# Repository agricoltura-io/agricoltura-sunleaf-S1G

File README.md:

# agricoltura-sunleaf-S1G
A new generation of the SunLeaf platform based on STM32 S1G radio module

Quick Specs:
- ST Microelectronics SPSGRF-915 STM32 ARM Cortex M0 915MHZ RF Module
- BQ240210 Lithium Ion Solar/USB charge controller and battery management 
- 500mA Lithium Polymer battery with thermistor 
- I2C ports
- UART ports
- Analog ports

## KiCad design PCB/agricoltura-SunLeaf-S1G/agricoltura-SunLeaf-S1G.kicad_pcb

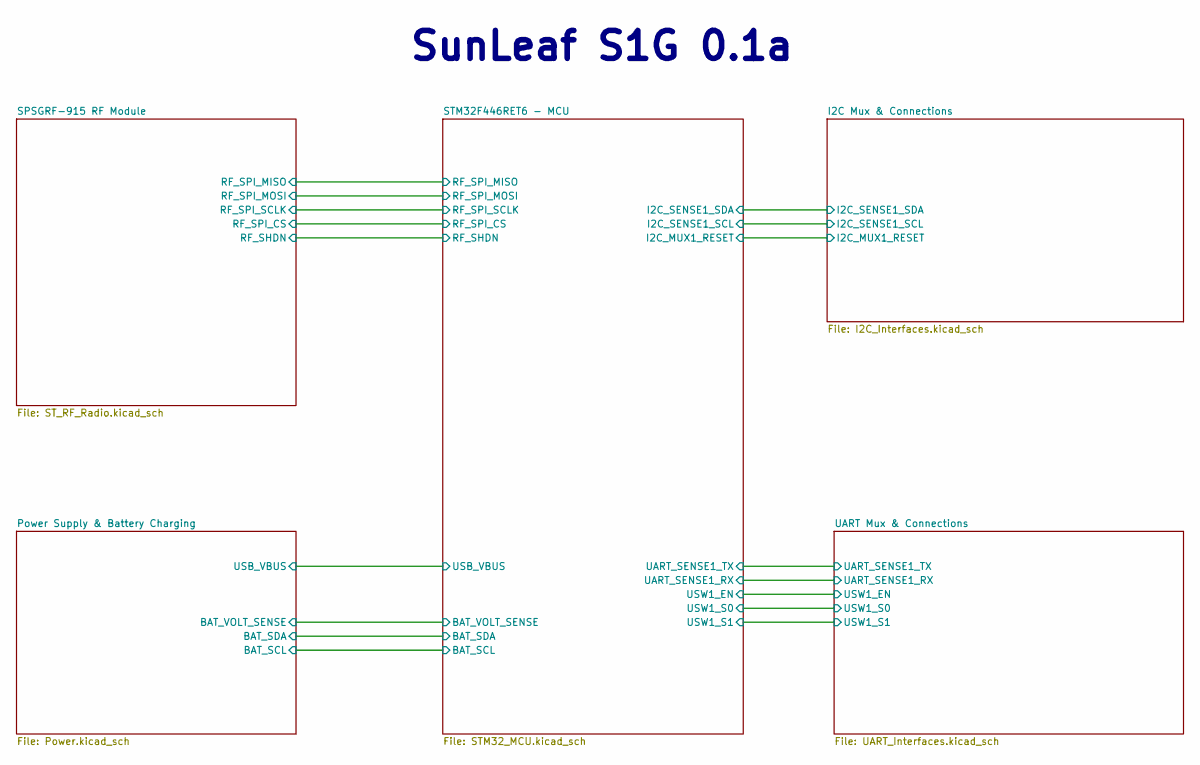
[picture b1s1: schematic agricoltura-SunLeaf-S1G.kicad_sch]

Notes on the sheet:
SunLeaf S1G 0.1a

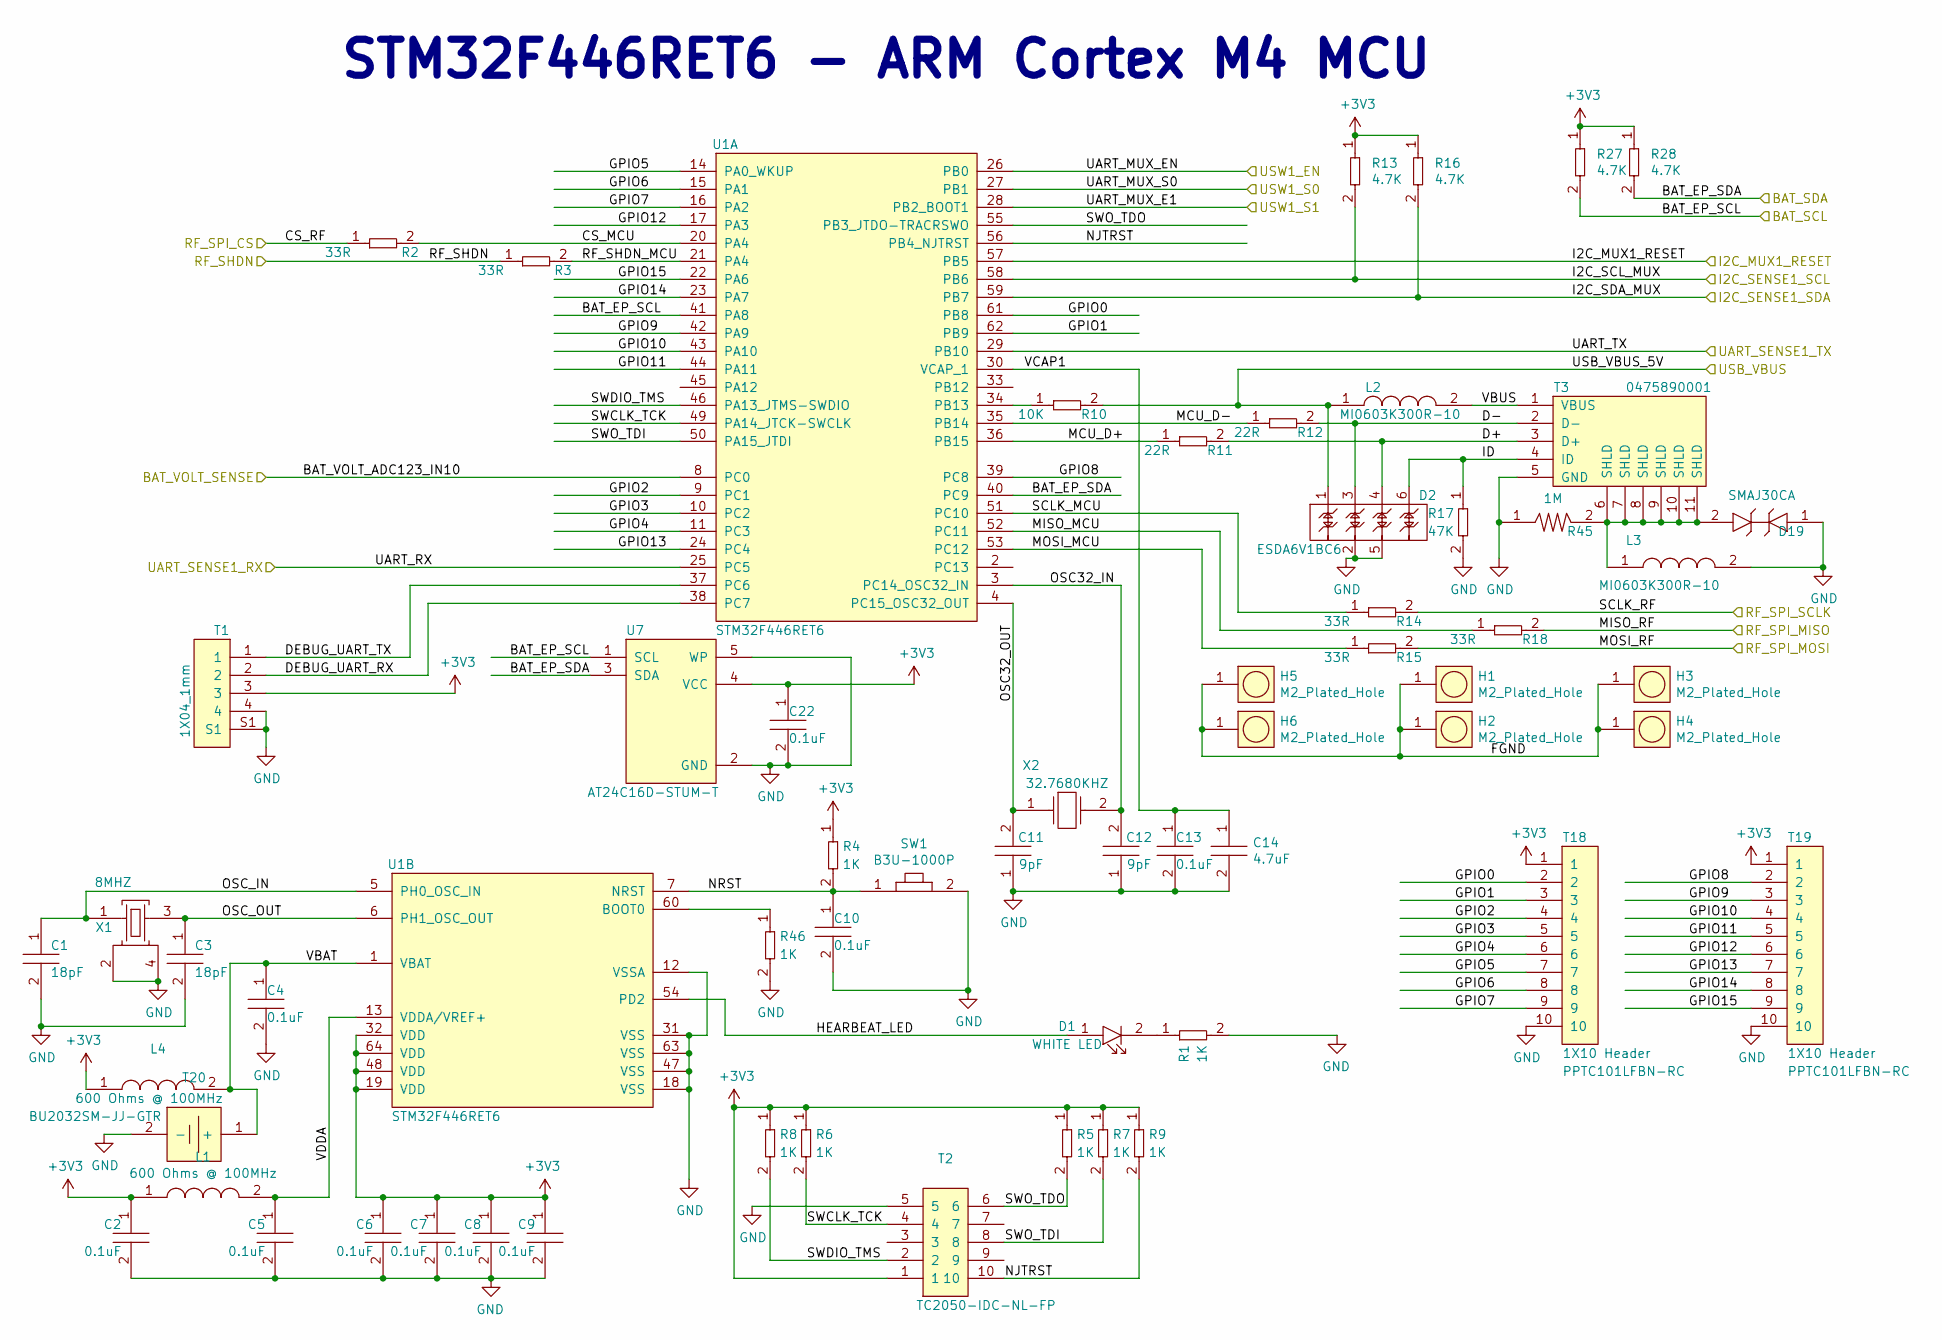
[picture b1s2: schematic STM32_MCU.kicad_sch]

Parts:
C1, C3: GCM1555C1H180GA16D; C0402; Tolerance 2%; Voltage 50V; MFR# GCM1555C1H180GA16D
C2, C4, C5, C6, C7, C8, C9, C10, C13, C22: C0402C104K9PACTU; R0402; Tolerance 10%; Voltage 6.3V; MFR# C0402C104K9PACTU
C11, C12: CL05C090CB5NNNC; C0402; Tolerance ±0.25pF; Voltage 50V; MFR# CL05C090CB5NNNC
C14: GRM155R60J475ME47D; C0402; Tolerance 20%; Voltage 6.3V; MFR# GRM155R60J475ME47D
D1: LW_Q38G_Q1OO_3K6L_1; LED0603; Tolerance *; Voltage 2.85V; MFR# LW Q38G-Q1OO-3K6L-1
D2: ESDA6V1BC6; SOT-23-6_Handsoldering; Tolerance *; Voltage 5V/6.1VBreakdown; MFR# ESDA6V1BC6
D19: SMAJ30CA; Tolerance *; Voltage 30V Clamp; MFR# SMAJ30CA
H1, H2, H3, H4, H5, H6: M2_Plated_Hole; M2_HOLE; Tolerance *; Voltage *; MFR# *
L1, L4: BLM15HG601SN1D; Tolerance *; Voltage *; MFR# BLM15HG601SN1D
L2, L3: MI0603K300R-10; Tolerance *; Voltage *; MFR# MI0603K300R-10
R1, R4, R5, R6, R7, R8, R9, R46: RC0402FR-071KL; R0402; Tolerance 1%; Voltage *; MFR# RC0402FR-071KL
R2, R3, R14, R15, R18: RC0402FR-0733RL; R0402; Tolerance 1%; Voltage *; MFR# RC0402FR-0733RL
R10: RC0402FR-0710KL; R0402; Tolerance 1%; Voltage *; MFR# RC0402FR-0710KL
R11, R12: RC0402FR-0722RL; R0402; Tolerance 1%; Voltage *; MFR# RC0402FR-0722RL
R13, R16, R27, R28: RC0402FR-074K7L; R0402; Tolerance 1%; Voltage *; MFR# RC0402FR-074K7L
R17: RC0603FR-0747KL; R0603; Tolerance 1%; Voltage *; MFR# RC0603FR-0747KL
R45: RC1206FR-071ML; R1206; Tolerance 1%; Voltage *; MFR# RC1206FR-071ML
SW1: B3U-1000P; Tolerance *; Voltage *; MFR# B3U-1000P
T1: BM04B-SRSS-TB(LF)(SN); CONN_BM04B-SRSS-TB(LF)(SN); Tolerance *; Voltage 50V; MFR# BM04B-SRSS-TB(LF)(SN)
T2: TC2050-IDC-NL-FP; TC2050-CLIP; Tolerance *; Voltage *; MFR# TC2050-IDC-NL-FP
T3: 0475890001; Tolerance *; Voltage 5V; MFR# 0475890001
T18, T19: PPTC101LFBN-RC; Female_Header_Straight_1x10_Pitch2.54mm; Tolerance *; Voltage 250V; MFR# PPTC101LFBN-RC
T20: BU2032SM-JJ-GTR; Tolerance *; Voltage 3.3V; MFR# BU2032SM-JJ-GTR
U1: STM32F446RET6; Tolerance *; Voltage 1.7V ~ 3.6V; MFR# STM32F446RET6
U7: AT24C16D-STUM-T; SOT-23-5; Tolerance *; Voltage 3.3V; MFR# AT24C16D-STUM-T
X1: ABM3B-8.000MHZ-B2-T; ABM3B8.000MHZB2T; Tolerance *; Voltage *; MFR# ABM3B-8.000MHZ-B2-T
X2: ABS07-32.768KHZ-9-T; Tolerance *; Voltage *; MFR# ABS07-32.768KHZ-9-T

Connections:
+3V3: C2.1, C6.1, C7.1, C8.1, C9.1, C22.1, L1.1, L4.1, R4.1, R5.1, R6.1, R7.1, R8.1, R9.1, R13.1, R16.1, R27.1, R28.1, T1.3, T2.1, T18.1, T19.1, U1.19 (VDD), U1.32 (VDD), U1.48 (VDD), U1.64 (VDD), U7.4 (VCC); also elsewhere on the board
/I2C Mux & Connections/I2C_MUX1_RESET: U1.57 (PB5); also elsewhere on the board
/I2C Mux & Connections/I2C_SENSE1_SCL: R13.2, U1.58 (PB6); also elsewhere on the board
/I2C Mux & Connections/I2C_SENSE1_SDA: R16.2, U1.59 (PB7); also elsewhere on the board
/Power Supply & Battery Charging/BAT_SCL: R27.2, U1.41 (PA8), U7.1 (SCL); also elsewhere on the board
/Power Supply & Battery Charging/BAT_SDA: R28.2, U1.40 (PC9), U7.3 (SDA); also elsewhere on the board
/Power Supply & Battery Charging/BAT_VOLT_SENSE: U1.8 (PC0); also elsewhere on the board
/Power Supply & Battery Charging/USB_VBUS: D2.1, L2.1, R10.2; also elsewhere on the board
/SPSGRF-915 RF Module /RF_SHDN: R3.1; also elsewhere on the board
/SPSGRF-915 RF Module /RF_SPI_CS: R2.1; also elsewhere on the board
/SPSGRF-915 RF Module /RF_SPI_MISO: R18.2; also elsewhere on the board
/SPSGRF-915 RF Module /RF_SPI_MOSI: R15.2; also elsewhere on the board
/SPSGRF-915 RF Module /RF_SPI_SCLK: R14.2; also elsewhere on the board
/STM32F446RET6 - MCU/CS_MCU: R2.2, U1.20 (PA4)
/STM32F446RET6 - MCU/D+: D2.4, R11.2, T3.3 (D+)
/STM32F446RET6 - MCU/D-: D2.3, R12.2, T3.2 (D-)
/STM32F446RET6 - MCU/DEBUG_UART_RX: T1.2, U1.38 (PC7)
/STM32F446RET6 - MCU/DEBUG_UART_TX: T1.1, U1.37 (PC6)
/STM32F446RET6 - MCU/FGND: H1.1, H2.1, H3.1, H4.1, H5.1, H6.1
/STM32F446RET6 - MCU/GPIO0: T18.2, U1.61 (PB8)
/STM32F446RET6 - MCU/GPIO1: T18.3, U1.62 (PB9)
/STM32F446RET6 - MCU/GPIO2: T18.4, U1.9 (PC1)
/STM32F446RET6 - MCU/GPIO3: T18.5, U1.10 (PC2)
/STM32F446RET6 - MCU/GPIO4: T18.6, U1.11 (PC3)
/STM32F446RET6 - MCU/GPIO5: T18.7, U1.14 (PA0_WKUP)
/STM32F446RET6 - MCU/GPIO6: T18.8, U1.15 (PA1)
/STM32F446RET6 - MCU/GPIO7: T18.9, U1.16 (PA2)
/STM32F446RET6 - MCU/GPIO8: T19.2, U1.39 (PC8)
/STM32F446RET6 - MCU/GPIO9: T19.3, U1.42 (PA9)
/STM32F446RET6 - MCU/GPIO10: T19.4, U1.43 (PA10)
/STM32F446RET6 - MCU/GPIO11: T19.5, U1.44 (PA11)
/STM32F446RET6 - MCU/GPIO12: T19.6, U1.17 (PA3)
/STM32F446RET6 - MCU/GPIO13: T19.7, U1.24 (PC4)
/STM32F446RET6 - MCU/GPIO14: T19.8, U1.23 (PA7)
/STM32F446RET6 - MCU/GPIO15: T19.9, U1.22 (PA6)
/STM32F446RET6 - MCU/HEARBEAT_LED: D1.1, U1.54 (PD2)
/STM32F446RET6 - MCU/ID: D2.6, R17.1, T3.4 (ID)
/STM32F446RET6 - MCU/MCU_D+: R11.1, U1.36 (PB15)
/STM32F446RET6 - MCU/MCU_D-: R12.1, U1.35 (PB14)
/STM32F446RET6 - MCU/MISO_MCU: R18.1, U1.52 (PC11)
/STM32F446RET6 - MCU/MOSI_MCU: R15.1, U1.53 (PC12)
/STM32F446RET6 - MCU/NJTRST: R9.2, T2.10, U1.56 (PB4_NJTRST)
/STM32F446RET6 - MCU/NRST: C10.1, R4.2, SW1.1, U1.7 (NRST)
/STM32F446RET6 - MCU/OSC32_IN: C12.2, U1.3 (PC14_OSC32_IN), X2.2
/STM32F446RET6 - MCU/OSC32_OUT: C11.2, U1.4 (PC15_OSC32_OUT), X2.1
/STM32F446RET6 - MCU/OSC_IN: C1.1, U1.5 (PH0_OSC_IN), X1.1
/STM32F446RET6 - MCU/OSC_OUT: C3.1, U1.6 (PH1_OSC_OUT), X1.3
/STM32F446RET6 - MCU/RF_SHDN_MCU: R3.2, U1.21 (PA4)
/STM32F446RET6 - MCU/SCLK_MCU: R14.1, U1.51 (PC10)
/STM32F446RET6 - MCU/SWCLK_TCK: R6.2, T2.4, U1.49 (PA14_JTCK-SWCLK)
/STM32F446RET6 - MCU/SWDIO_TMS: R8.2, T2.2, U1.46 (PA13_JTMS-SWDIO)
/STM32F446RET6 - MCU/SWO_TDI: R7.2, T2.8, U1.50 (PA15_JTDI)
/STM32F446RET6 - MCU/SWO_TDO: R5.2, T2.6, U1.55 (PB3_JTDO-TRACRSWO)
/STM32F446RET6 - MCU/UART_SENSE1_RX: U1.25 (PC5); also elsewhere on the board
/STM32F446RET6 - MCU/UART_SENSE1_TX: U1.29 (PB10); also elsewhere on the board
/STM32F446RET6 - MCU/USW1_EN: U1.26 (PB0); also elsewhere on the board
/STM32F446RET6 - MCU/USW1_S0: U1.27 (PB1); also elsewhere on the board
/STM32F446RET6 - MCU/USW1_S1: U1.28 (PB2_BOOT1); also elsewhere on the board
/STM32F446RET6 - MCU/VBAT: C4.1, L4.2, T20.1 (+), U1.1 (VBAT)
/STM32F446RET6 - MCU/VBUS: L2.2, T3.1 (VBUS)
/STM32F446RET6 - MCU/VCAP1: C13.1, C14.1, U1.30 (VCAP_1)
/STM32F446RET6 - MCU/VDDA: C5.1, L1.2, U1.13 (VDDA/VREF+)
GND: C1.2, C2.2, C3.2, C4.2, C5.2, C6.2, C7.2, C8.2, C9.2, C10.2, C11.1, C12.1, C13.2, C14.2, C22.2, D2.2, D2.5, D19.1, L3.2, R1.2, R17.2, R45.1, R46.2, SW1.2, T1.4, T1.S1, T2.5, T3.5 (GND), T18.10, T19.10, T20.2 (-), U1.12 (VSSA), U1.18 (VSS), U1.31 (VSS), U1.47 (VSS), U1.63 (VSS), U7.2 (GND), U7.5 (WP), X1.2, X1.4; also elsewhere on the board
unnamed: D1.2, R1.1
unnamed: D19.2, L3.1, R45.2, T3.6 (SHLD), T3.7 (SHLD), T3.8 (SHLD), T3.9 (SHLD), T3.10 (SHLD), T3.11 (SHLD)
unnamed: R10.1, U1.34 (PB13)
unnamed: R46.1, U1.60 (BOOT0)

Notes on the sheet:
STM32F446RET6 - ARM Cortex M4 MCU

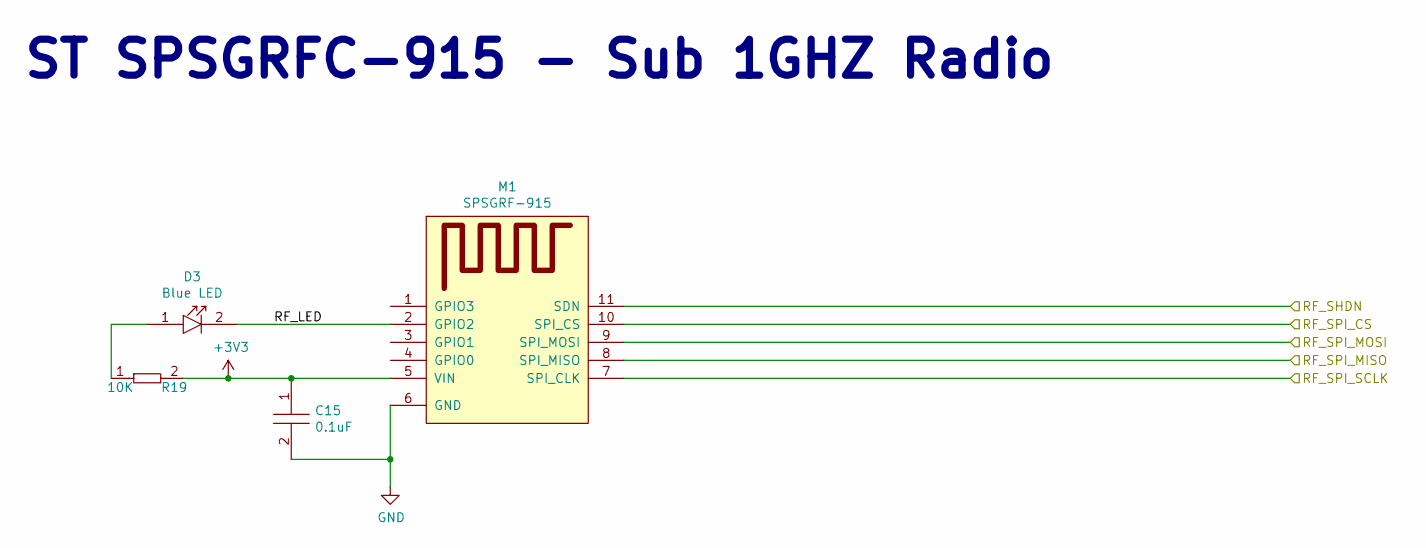
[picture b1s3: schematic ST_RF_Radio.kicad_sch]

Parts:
C15: C0402C104K9PACTU; R0402; Tolerance 10%; Voltage 6.3V; MFR# C0402C104K9PACTU
D3: LTST-C194TBKT; LED0603; Tolerance *; Voltage 3.3V; MFR# LTST-C194TBKT
M1: SPSGRF-915; XCVR_SPSGRF-915; Tolerance *; Voltage 1.8V ~ 3.6V; MFR# SPSGRF-915
R19: RC0402FR-0710KL; R0402; Tolerance 1%; Voltage *; MFR# RC0402FR-0710KL

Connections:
+3V3: C15.1, M1.5 (VIN), R19.2; also elsewhere on the board
/SPSGRF-915 RF Module /RF_LED: D3.2, M1.2 (GPIO2)
/SPSGRF-915 RF Module /RF_SHDN: M1.11 (SDN); also elsewhere on the board
/SPSGRF-915 RF Module /RF_SPI_CS: M1.10 (SPI_CS); also elsewhere on the board
/SPSGRF-915 RF Module /RF_SPI_MISO: M1.8 (SPI_MISO); also elsewhere on the board
/SPSGRF-915 RF Module /RF_SPI_MOSI: M1.9 (SPI_MOSI); also elsewhere on the board
/SPSGRF-915 RF Module /RF_SPI_SCLK: M1.7 (SPI_CLK); also elsewhere on the board
GND: C15.2, M1.6 (GND); also elsewhere on the board
unnamed: D3.1, R19.1

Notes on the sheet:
ST SPSGRFC-915 - Sub 1GHZ Radio

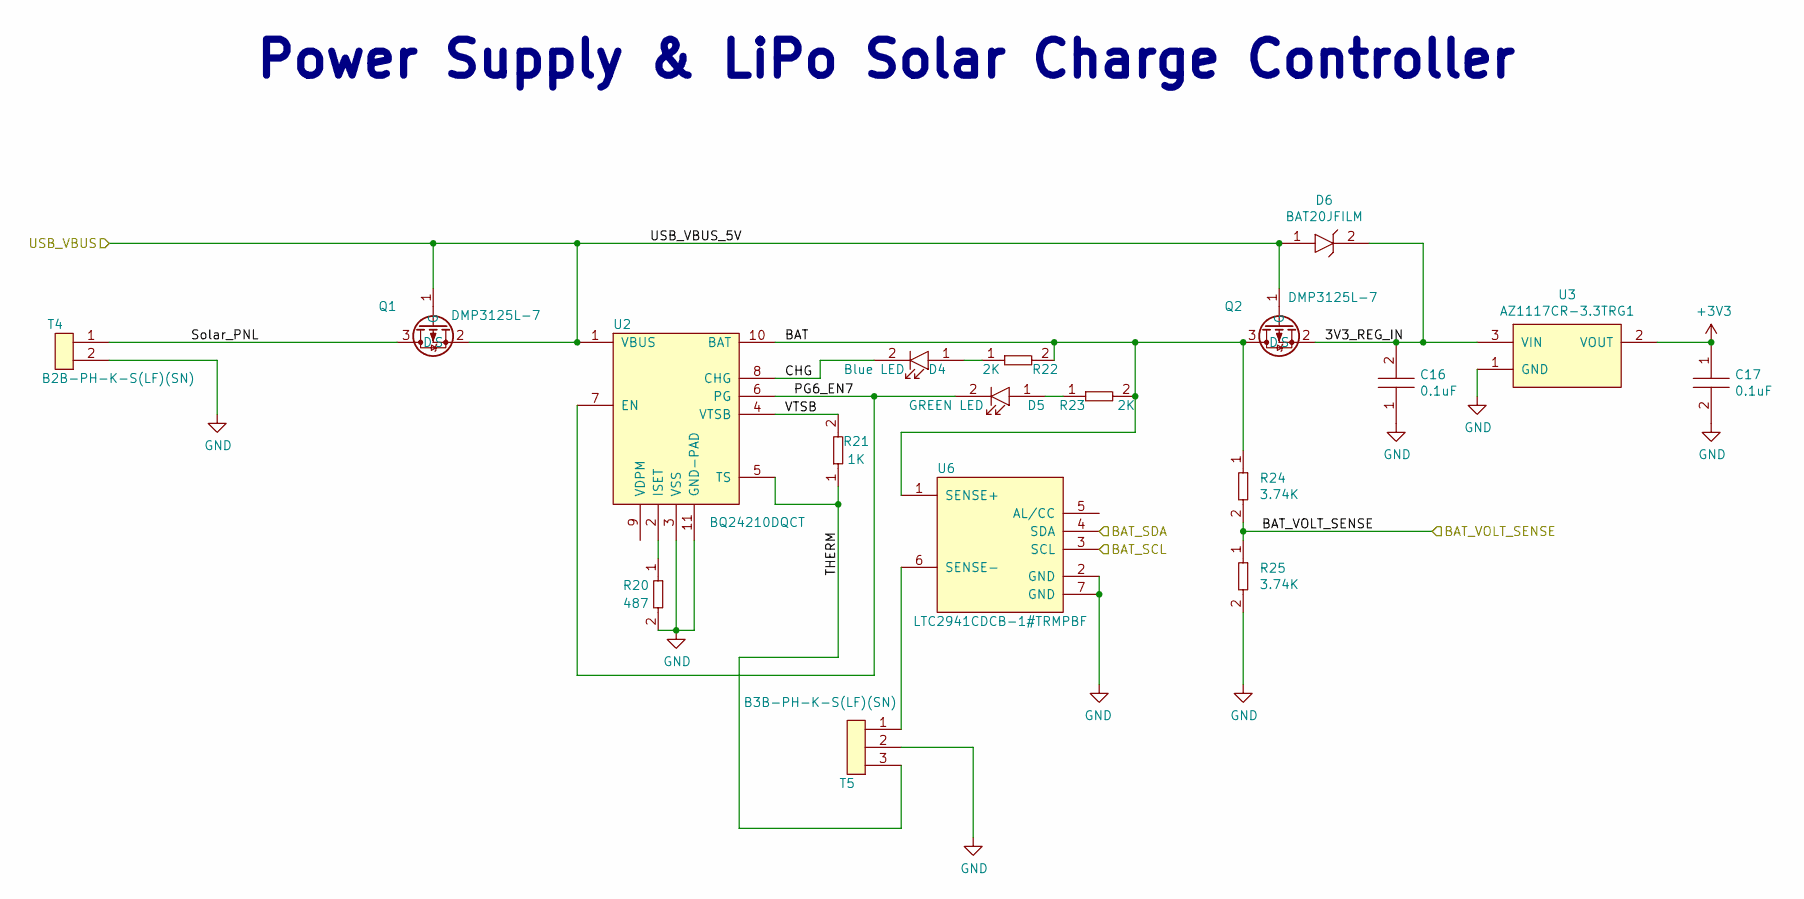
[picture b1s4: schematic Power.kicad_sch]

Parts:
C16: C0805C104M5RACTU; C0805; Tolerance 20%; Voltage 50V; MFR# C0805C104M5RACTU
C17: C0402C104K9PACTU; R0402; Tolerance 10%; Voltage 6.3V; MFR# C0402C104K9PACTU
D4: LTST-C194TBKT; LED0603; Tolerance *; Voltage 3.3V; MFR# LTST-C194TBKT
D5: LTST-C194KGKT; LED0603; Tolerance *; Voltage 2.1V; MFR# LTST-C194KGKT
D6: BAT20JFILM; Tolerance *; Voltage 23V; MFR# BAT20JFILM
Q1, Q2: DMP3125L-7; SOT-23; Tolerance *; Voltage 20V; MFR# DMP3125L-7
R20: RC0402FR-07487RL; R0402; Tolerance 1%; Voltage *; MFR# RC0402FR-07487RL
R21: RC0402FR-071KL; R0402; Tolerance 1%; Voltage *; MFR# RC0402FR-071KL
R22, R23: RC0402FR-072KL; R0402; Tolerance 1%; Voltage *; MFR# RC0402FR-072KL
R24, R25: ERA-3AEB3741V; R0603; Tolerance 1%; Voltage *; MFR# ERA-3AEB3741V
T4: B2B-PH-K-S(LF)(SN); Tolerance *; Voltage 100V; MFR# B2B-PH-K-S(LF)(SN)
T5: B3B-PH-K-S(LF)(SN); Tolerance *; Voltage 100V; MFR# B3B-PH-K-S(LF)(SN)
U2: BQ24210DQCT; BQ24210; Tolerance *; Voltage 18V MAX IN, 4.2V BATT MAX; MFR# BQ24210DQCT
U3: AZ1117CR-3.3TRG1; SOT_89; Tolerance *; Voltage 15IN, 3V3 OUT; MFR# AZ1117CR-3.3TRG1
U6: LTC2941CDCB-1#TRMPBF; LTC2941CDCB-1-TRMPBF; Tolerance *; Voltage *; MFR# LTC2941CDCB-1#TRMPBF

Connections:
+3V3: C17.1, U3.2 (VOUT); also elsewhere on the board
/Power Supply & Battery Charging/3V3_REG_IN: C16.2, D6.2, Q2.2 (S), U3.3 (VIN)
/Power Supply & Battery Charging/BAT: Q2.3 (D), R22.2, R23.2, R24.1, U2.10 (BAT), U6.1 (SENSE+)
/Power Supply & Battery Charging/BAT_SCL: U6.3 (SCL); also elsewhere on the board
/Power Supply & Battery Charging/BAT_SDA: U6.4 (SDA); also elsewhere on the board
/Power Supply & Battery Charging/BAT_VOLT_SENSE: R24.2, R25.1; also elsewhere on the board
/Power Supply & Battery Charging/CHG: D4.2, U2.8 (CHG)
/Power Supply & Battery Charging/PG6_EN7: D5.2, U2.6 (PG), U2.7 (EN)
/Power Supply & Battery Charging/Solar_PNL: Q1.3 (D), T4.1
/Power Supply & Battery Charging/THERM: R21.1, T5.3, U2.5 (TS)
/Power Supply & Battery Charging/USB_VBUS: D6.1, Q1.1 (G), Q1.2 (S), Q2.1 (G), U2.1 (VBUS); also elsewhere on the board
/Power Supply & Battery Charging/VTSB: R21.2, U2.4 (VTSB)
GND: C16.1, C17.2, R20.2, R25.2, T4.2, T5.2, U2.3 (VSS), U2.11 (GND-PAD), U3.1 (GND), U6.2 (GND), U6.7 (GND); also elsewhere on the board
unnamed: D4.1, R22.1
unnamed: D5.1, R23.1
unnamed: R20.1, U2.2 (ISET)
unnamed: T5.1, U6.6 (SENSE-)

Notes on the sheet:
Power Supply & LiPo Solar Charge Controller

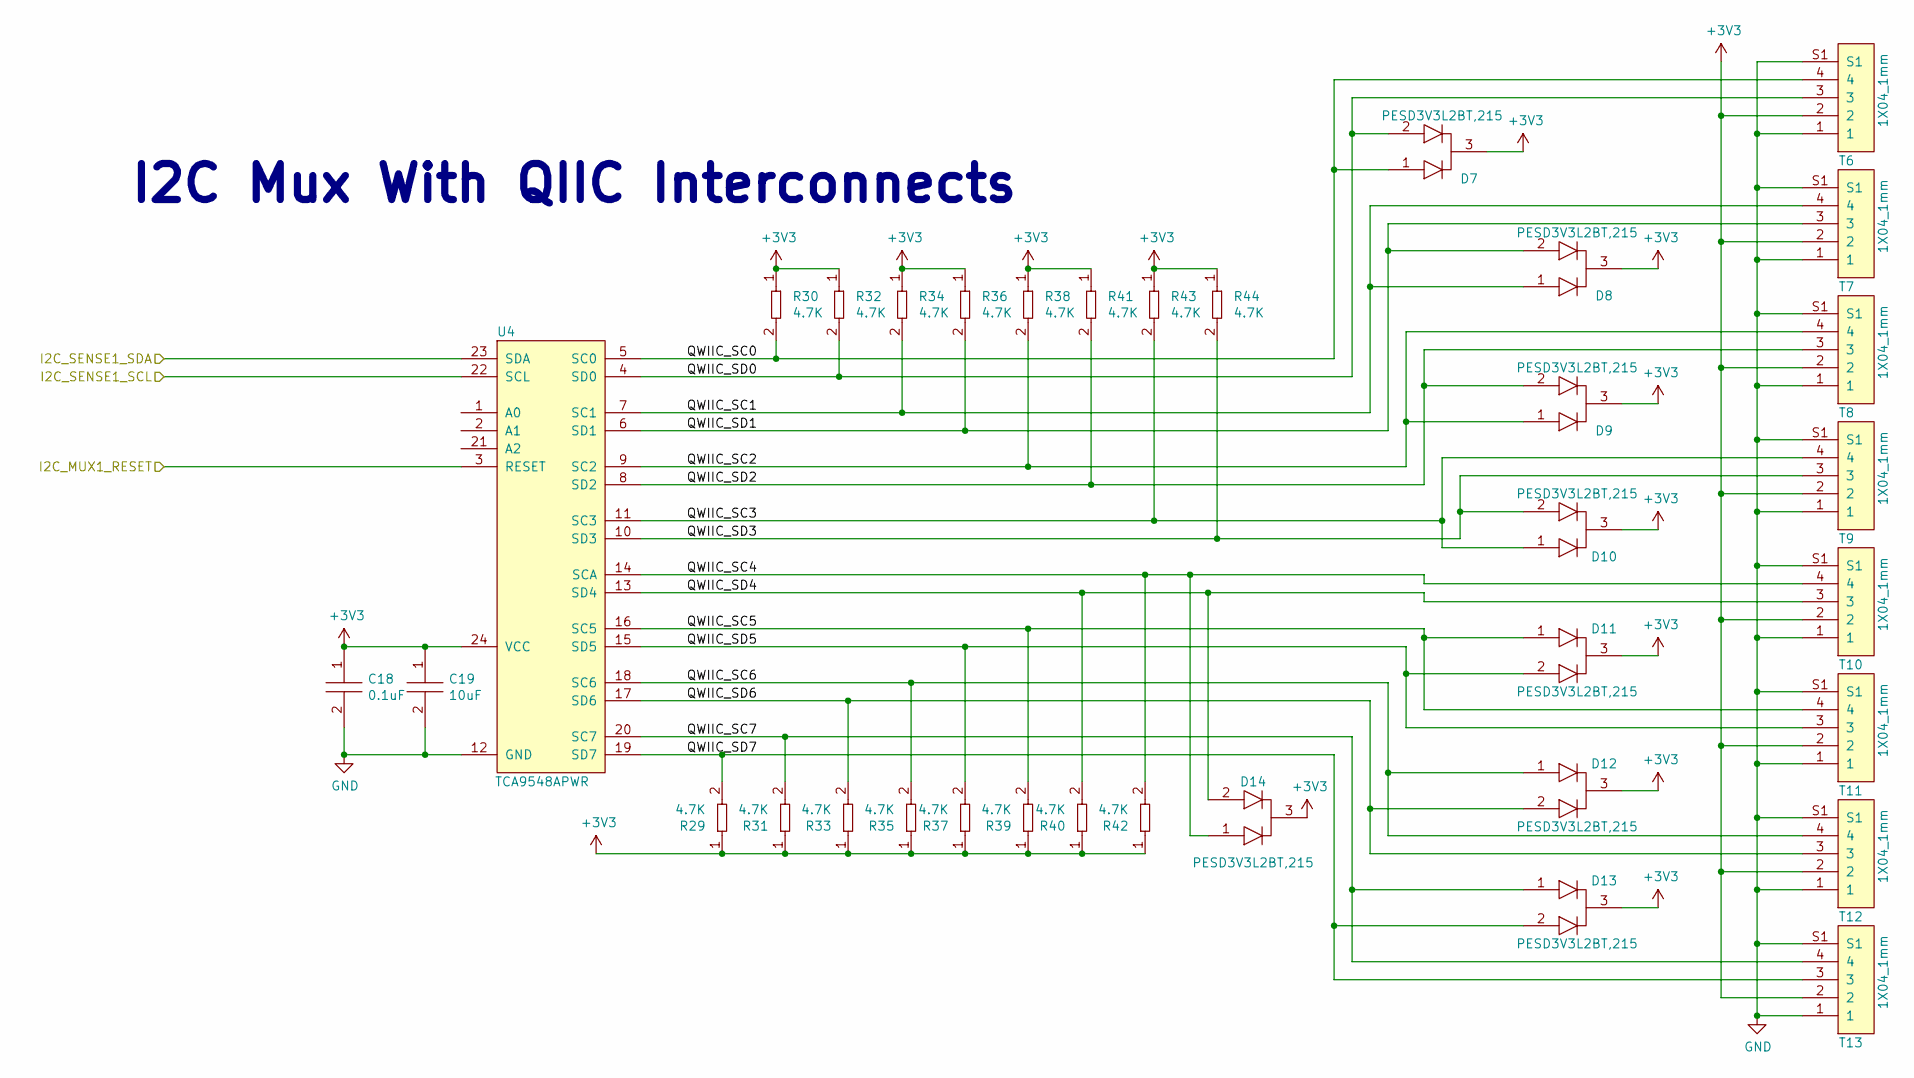
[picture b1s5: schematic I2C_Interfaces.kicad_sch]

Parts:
C18: C0402C104K9PACTU; R0402; Tolerance 10%; Voltage 6.3V; MFR# C0402C104K9PACTU
C19: GRM188R61A106KE69J; C0603; Tolerance 10%; Voltage 10V; MFR# GRM188R61A106KE69J
D7, D8, D9, D10, D11, D12, D13, D14: PESD3V3L2BT,215; SOT-23; Tolerance *; Voltage *; MFR# PESD3V3L2BT,215
R29, R30, R31, R32, R33, R34, R35, R36, R37, R38, R39, R40, R41, R42, R43, R44: RC0402FR-074K7L; R0402; Tolerance 1%; Voltage *; MFR# RC0402FR-074K7L
T6, T7, T8, T9, T10, T11, T12, T13: BM04B-SRSS-TB(LF)(SN); CONN_BM04B-SRSS-TB(LF)(SN); Tolerance *; Voltage 50V; MFR# BM04B-SRSS-TB(LF)(SN)
U4: TCA9548APWR; Tolerance *; Voltage 1.65V ~ 5.5V; MFR# TCA9548APWR

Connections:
+3V3: C18.1, C19.1, D7.3, D8.3, D9.3, D10.3, D11.3, D12.3, D13.3, D14.3, R29.1, R30.1, R31.1, R32.1, R33.1, R34.1, R35.1, R36.1, R37.1, R38.1, R39.1, R40.1, R41.1, R42.1, R43.1, R44.1, T6.2, T7.2, T8.2, T9.2, T10.2, T11.2, T12.2, T13.2, U4.24 (VCC); also elsewhere on the board
/I2C Mux & Connections/I2C_MUX1_RESET: U4.3 (RESET); also elsewhere on the board
/I2C Mux & Connections/I2C_SENSE1_SCL: U4.22 (SCL); also elsewhere on the board
/I2C Mux & Connections/I2C_SENSE1_SDA: U4.23 (SDA); also elsewhere on the board
/I2C Mux & Connections/QWIIC_SC0: D7.1, R30.2, T6.4, U4.5 (SC0)
/I2C Mux & Connections/QWIIC_SC1: D8.1, R34.2, T7.4, U4.7 (SC1)
/I2C Mux & Connections/QWIIC_SC2: D9.1, R38.2, T8.4, U4.9 (SC2)
/I2C Mux & Connections/QWIIC_SC3: D10.1, R43.2, T9.4, U4.11 (SC3)
/I2C Mux & Connections/QWIIC_SC4: D14.1, R42.2, T10.4, U4.14 (SCA)
/I2C Mux & Connections/QWIIC_SC5: D11.1, R39.2, T11.4, U4.16 (SC5)
/I2C Mux & Connections/QWIIC_SC6: D12.1, R35.2, T12.4, U4.18 (SC6)
/I2C Mux & Connections/QWIIC_SC7: D13.1, R31.2, T13.4, U4.20 (SC7)
/I2C Mux & Connections/QWIIC_SD0: D7.2, R32.2, T6.3, U4.4 (SD0)
/I2C Mux & Connections/QWIIC_SD1: D8.2, R36.2, T7.3, U4.6 (SD1)
/I2C Mux & Connections/QWIIC_SD2: D9.2, R41.2, T8.3, U4.8 (SD2)
/I2C Mux & Connections/QWIIC_SD3: D10.2, R44.2, T9.3, U4.10 (SD3)
/I2C Mux & Connections/QWIIC_SD4: D14.2, R40.2, T10.3, U4.13 (SD4)
/I2C Mux & Connections/QWIIC_SD5: D11.2, R37.2, T11.3, U4.15 (SD5)
/I2C Mux & Connections/QWIIC_SD6: D12.2, R33.2, T12.3, U4.17 (SD6)
/I2C Mux & Connections/QWIIC_SD7: D13.2, R29.2, T13.3, U4.19 (SD7)
GND: C18.2, C19.2, T6.1, T6.S1, T7.1, T7.S1, T8.1, T8.S1, T9.1, T9.S1, T10.1, T10.S1, T11.1, T11.S1, T12.1, T12.S1, T13.1, T13.S1, U4.12 (GND); also elsewhere on the board

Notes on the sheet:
I2C Mux With QIIC Interconnects

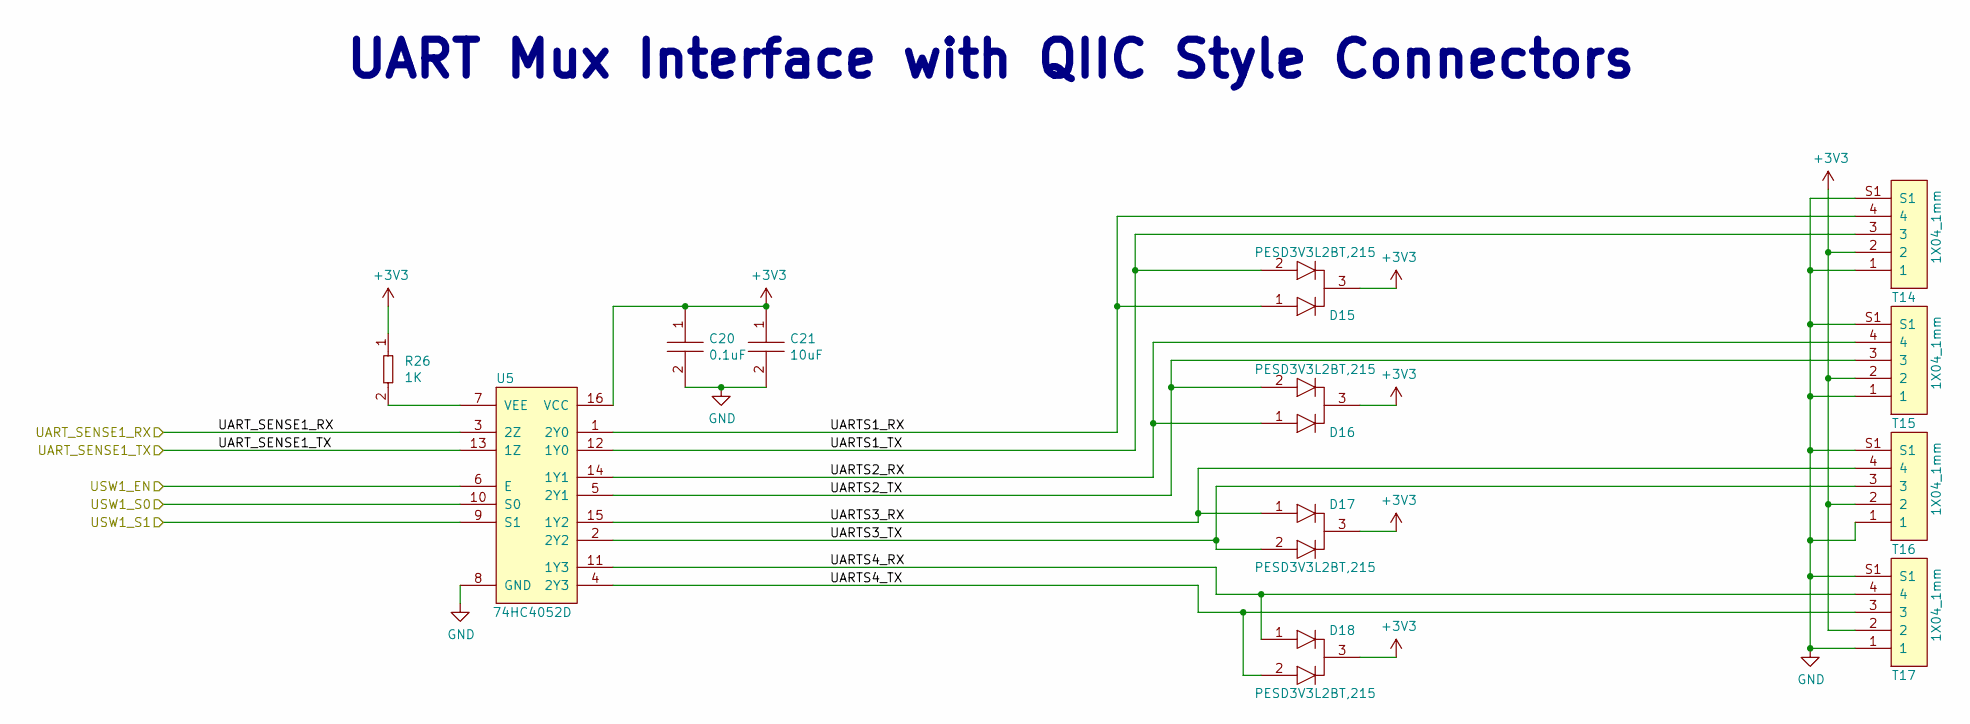
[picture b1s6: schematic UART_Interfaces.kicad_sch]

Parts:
C20: C0402C104K9PACTU; R0402; Tolerance 10%; Voltage 6.3V; MFR# C0402C104K9PACTU
C21: GRM188R61A106KE69J; C0603; Tolerance 10%; Voltage 10V; MFR# GRM188R61A106KE69J
D15, D16, D17, D18: PESD3V3L2BT,215; SOT-23; Tolerance *; Voltage *; MFR# PESD3V3L2BT,215
R26: RC0402FR-071KL; R0402; Tolerance 1%; Voltage *; MFR# RC0402FR-071KL
T14, T15, T16, T17: BM04B-SRSS-TB(LF)(SN); CONN_BM04B-SRSS-TB(LF)(SN); Tolerance *; Voltage 50V; MFR# BM04B-SRSS-TB(LF)(SN)
U5: 74HC4052D; Tolerance *; Voltage 2V ~ 6V; MFR# 74HC4052D

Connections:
+3V3: C20.1, C21.1, D15.3, D16.3, D17.3, D18.3, R26.1, T14.2, T15.2, T16.2, T17.2, U5.16 (VCC); also elsewhere on the board
/STM32F446RET6 - MCU/UART_SENSE1_RX: U5.3 (2Z); also elsewhere on the board
/STM32F446RET6 - MCU/UART_SENSE1_TX: U5.13 (1Z); also elsewhere on the board
/STM32F446RET6 - MCU/USW1_EN: U5.6 (E); also elsewhere on the board
/STM32F446RET6 - MCU/USW1_S0: U5.10 (S0); also elsewhere on the board
/STM32F446RET6 - MCU/USW1_S1: U5.9 (S1); also elsewhere on the board
/UART Mux & Connections/UARTS1_RX: D15.1, T14.4, U5.1 (2Y0)
/UART Mux & Connections/UARTS1_TX: D15.2, T14.3, U5.12 (1Y0)
/UART Mux & Connections/UARTS2_RX: D16.1, T15.4, U5.14 (1Y1)
/UART Mux & Connections/UARTS2_TX: D16.2, T15.3, U5.5 (2Y1)
/UART Mux & Connections/UARTS3_RX: D17.1, T16.4, U5.15 (1Y2)
/UART Mux & Connections/UARTS3_TX: D17.2, T16.3, U5.2 (2Y2)
/UART Mux & Connections/UARTS4_RX: D18.1, T17.4, U5.11 (1Y3)
/UART Mux & Connections/UARTS4_TX: D18.2, T17.3, U5.4 (2Y3)
GND: C20.2, C21.2, T14.1, T14.S1, T15.1, T15.S1, T16.1, T16.S1, T17.1, T17.S1, U5.8 (GND); also elsewhere on the board
unnamed: R26.2, U5.7 (VEE)

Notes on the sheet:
UART Mux Interface with QIIC Style Connectors

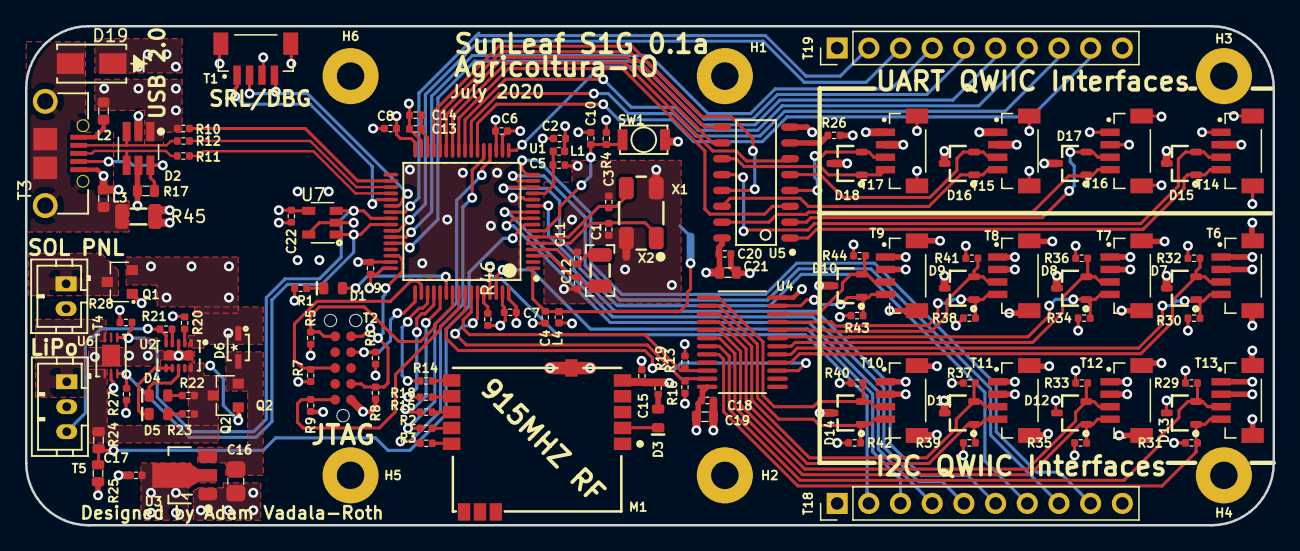
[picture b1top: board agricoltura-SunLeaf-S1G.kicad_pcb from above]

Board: 4 copper layers, 100.0 x 40.0 mm, 130 parts (1 on the bottom side), 105 nets.

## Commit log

2020-07-08 Schematic Progress
    Schematic struture created, copied over circuits from Vine that are identical.
2020-07-10 Power Supply and Datasheets
    Added datasheets for parts in use, designed power supply circuit
2020-07-12 Schematic Complete
    Schematic completed and PCB started
2020-07-13 PCB Progress
    added TVS diodes fo QWIIC connector serial signals. Did more routing overall.
2020-07-18 Pullups
    Added pullup reistors to I2C ports, changed JTAG connector over to Tag connect.
2020-07-19 PCB Progress
    PCB routing progress made, USB port replaced with micro b like older sunleaf designs.
2020-07-20 Routing Complete
    Board routing completed, also added EEPROM for storing configuration settings.
2020-07-22 Adjusted Copper
    Adjusted copper pours and via placement underneath MCU
2021-02-26 Pix
    Pictures added
2024-03-26 Create license.md
    added license
2024-03-26 KiCAD 8
    Projected updated to KiCAD 8

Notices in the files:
parts and their libraries:
Copyright 2016 Accelerated Designs. All rights reserved.
